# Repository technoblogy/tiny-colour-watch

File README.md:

# Tiny Colour Watch
A watch based on an ATtiny85 using 12 APA102 RGB LEDs, arranged like a clock face, to show the time analogue-style.
For more information see: http://www.technoblogy.com/show?1Y7J.

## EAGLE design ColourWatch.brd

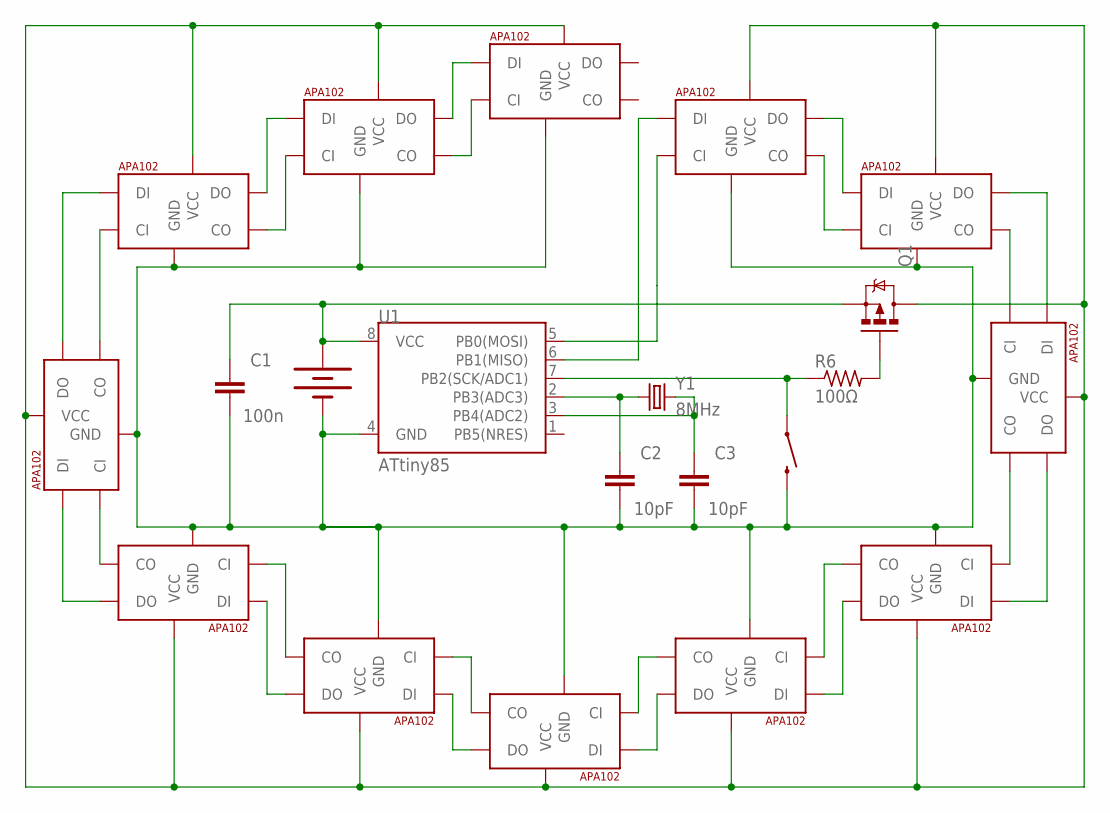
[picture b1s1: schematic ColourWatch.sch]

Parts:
1, 2, 3, 4, 5, 6, 7, 8, 9, 10, 11, 12: APA1022020; APA102_2020
BAT1: 20mm coincell; BATTCON_20MM_4LEGS
C1: 100n; 0603-CAP
C2, C3: 10pF; 0603-CAP
Q1: MOSFET-PCHANNELSMD; SOT23-3
R6: 100Ω; M0805
S2: SWITCH-MOMENTARY-2SMD; TACTILE-SWITCH-SMD
U1: ATtiny85; SO08-EIAJ
Y1: 8MHz; CRYSTAL-SMD-5X3

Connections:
unnamed: 2.CL_OUT (CO), 3.C_IN (CI)
unnamed: 3.D_OUT (DO), 4.D_IN (DI)
unnamed: 1.CL_OUT (CO), 2.C_IN (CI)
unnamed: 1.D_OUT (DO), 2.D_IN (DI)
unnamed: 2.D_OUT (DO), 3.D_IN (DI)
unnamed: 4.CL_OUT (CO), 5.C_IN (CI)
unnamed: 4.D_OUT (DO), 5.D_IN (DI)
unnamed: 1.GND, 2.GND, 3.GND, 4.GND, 5.GND, 6.GND, 7.GND, 8.GND, 9.GND, 10.GND, 11.GND, 12.GND, BAT1.NEGATIVE (-), C1.2, C2.2, C3.2, S2.3 (2), U1.4 (GND)
unnamed: C3.1, U1.3 (PB4(ADC2)), Y1.3 (2)
unnamed: C2.1, U1.2 (PB3(ADC3)), Y1.1
unnamed: R6.1, S2.1, U1.7 (PB2(SCK/ADC1))
unnamed: BAT1.POSITIVE@1 (+), BAT1.POSITIVE@2 (+), BAT1.POSITIVE@3 (+), BAT1.POSITIVE@4 (+), C1.1, Q1.2 (S), U1.8 (VCC)
unnamed: 1.V_CC (VCC), 2.V_CC (VCC), 3.V_CC (VCC), 4.V_CC (VCC), 5.V_CC (VCC), 6.V_CC (VCC), 7.V_CC (VCC), 8.V_CC (VCC), 9.V_CC (VCC), 10.V_CC (VCC), 11.V_CC (VCC), 12.V_CC (VCC), Q1.3 (D)
unnamed: 1.D_IN (DI), U1.6 (PB1(MISO))
unnamed: 5.CL_OUT (CO), 6.C_IN (CI)
unnamed: 5.D_OUT (DO), 6.D_IN (DI)
unnamed: 6.D_OUT (DO), 7.D_IN (DI)
unnamed: 6.CL_OUT (CO), 7.C_IN (CI)
unnamed: 7.D_OUT (DO), 8.D_IN (DI)
unnamed: 7.CL_OUT (CO), 8.C_IN (CI)
unnamed: 8.D_OUT (DO), 9.D_IN (DI)
unnamed: 3.CL_OUT (CO), 4.C_IN (CI)
unnamed: 9.D_OUT (DO), 10.D_IN (DI)
unnamed: 11.D_OUT (DO), 12.D_IN (DI)
unnamed: 11.CL_OUT (CO), 12.C_IN (CI)
unnamed: 10.CL_OUT (CO), 11.C_IN (CI)
unnamed: 10.D_OUT (DO), 11.D_IN (DI)
unnamed: 9.CL_OUT (CO), 10.C_IN (CI)
unnamed: 8.CL_OUT (CO), 9.C_IN (CI)
unnamed: 1.C_IN (CI), U1.5 (PB0(MOSI))
unnamed: Q1.1 (G), R6.2

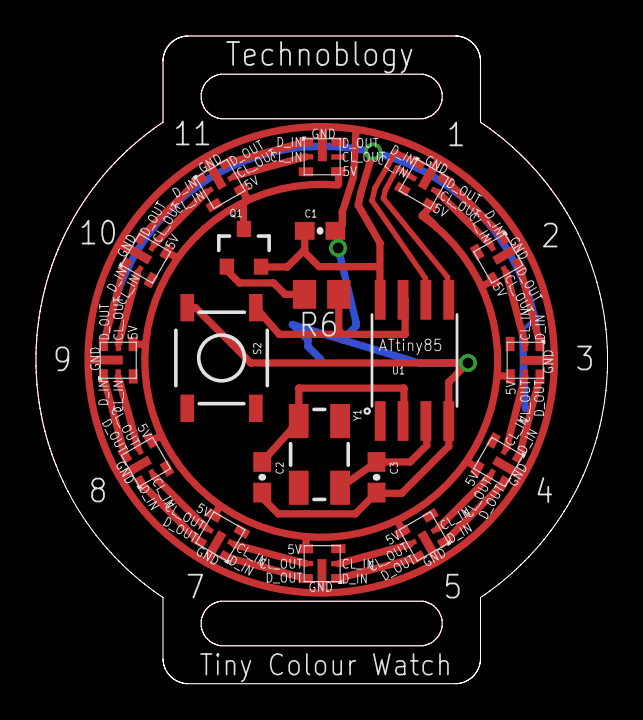
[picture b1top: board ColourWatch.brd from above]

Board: 2 copper layers, 31.7 x 36.0 mm, 21 parts (1 on the bottom side), 31 nets.

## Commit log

2018-01-15 Version 1 - 15th January 2018
2018-01-15 Version 1 - Eagle files

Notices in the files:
parts and their libraries:
SparkFun-DigitalIC: Licensing: Creative Commons ShareAlike 4.0 International - https://creativecommons.org/licenses/by-sa/4.0
SparkFun-Capacitors: Licensing: CC v3.0 Share-Alike You are welcome to use this library for commercial purposes.
